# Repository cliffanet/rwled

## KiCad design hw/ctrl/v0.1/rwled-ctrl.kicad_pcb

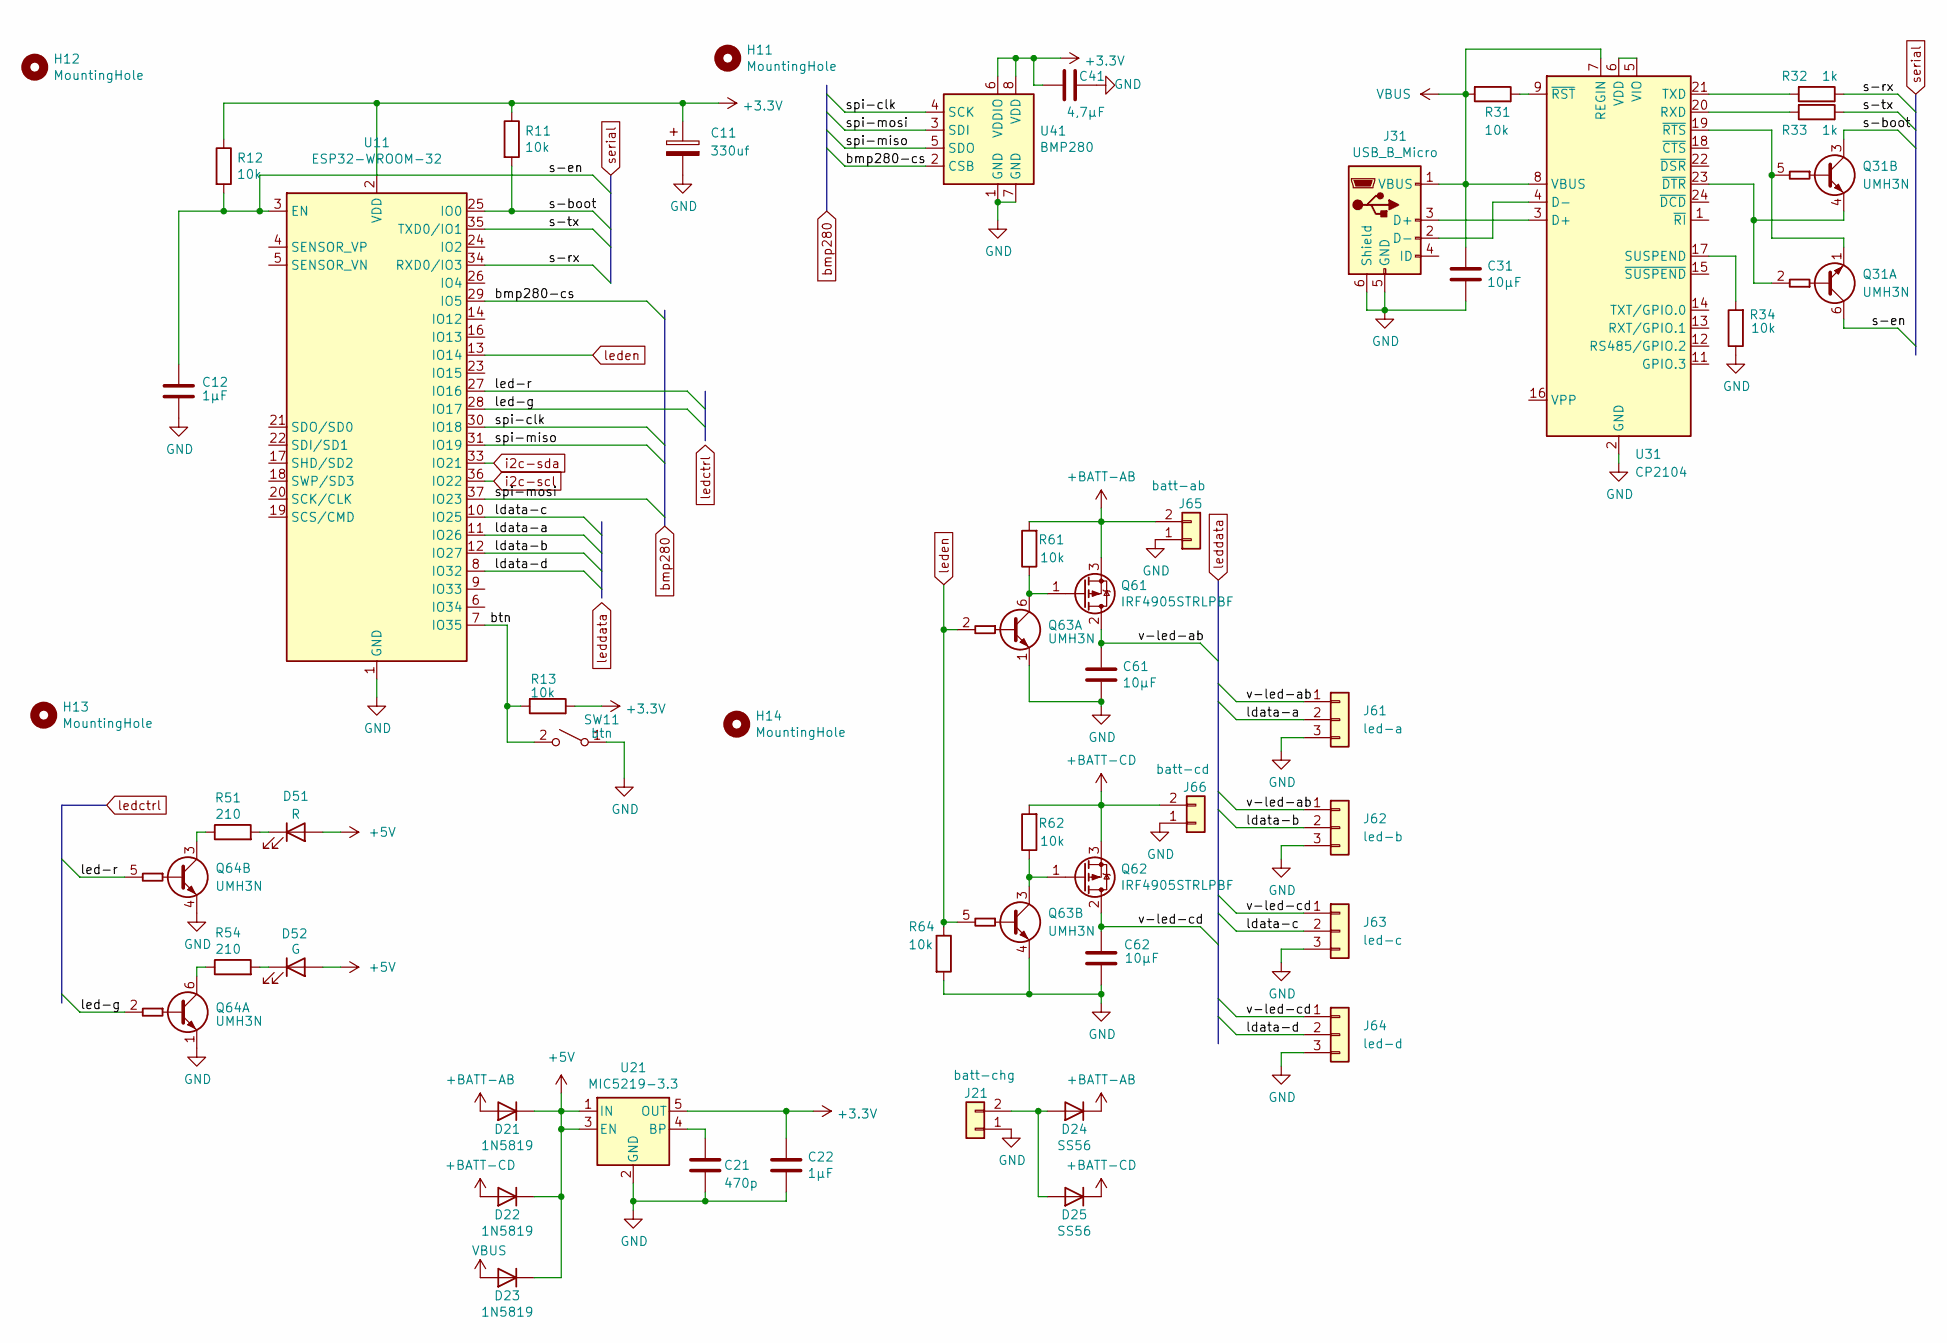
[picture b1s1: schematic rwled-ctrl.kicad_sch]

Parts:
C11: 330uf; CP_EIA-7343-20_Kemet-V
C12, C22: 1μF; C_0805_2012Metric
C21: 470p; C_0805_2012Metric
C31, C61, C62: 10μF; C_0805_2012Metric
C41: 4,7μF; C_0805_2012Metric
D21, D22, D23: 1N5819; D_SOD-323
D24, D25: SS56; D_SMA
D51: R; LED_D3.0mm
D52: G; LED_D3.0mm
H11, H12, H13, H14: MountingHole; MountingHole_3.2mm_M3
J21: batt-chg; AMASS_XT30U-M_1x02_P5.0mm_Vertical
J31: USB_B_Micro; USB_Micro-B_Molex-105017-0001
J61: led-a; JST_XH_S3B-XH-A_1x03_P2.50mm_Horizontal
J62: led-b; JST_XH_S3B-XH-A_1x03_P2.50mm_Horizontal
J63: led-c; JST_XH_S3B-XH-A_1x03_P2.50mm_Horizontal
J64: led-d; JST_XH_S3B-XH-A_1x03_P2.50mm_Horizontal
J65: batt-ab; AMASS_XT30U-F_1x02_P5.0mm_Vertical
J66: batt-cd; AMASS_XT30U-F_1x02_P5.0mm_Vertical
Q31, Q63, Q64: UMH3N; SOT-363_SC-70-6
Q61, Q62: IRF4905STRLPBF; TO-263-2
R11, R12, R13, R31, R34, R61, R62, R64: 10k; R_0805_2012Metric
R32, R33: 1k; R_0805_2012Metric
R51, R54: 210; R_1206_3216Metric
SW11: btn; SW_Push_1P1T_NO_6x6mm_H9.5mm
U11: ESP32-WROOM-32
U21: MIC5219-3.3; SOT-23-5
U31: CP2104; QFN-24-1EP_4x4mm_P0.5mm_EP2.6x2.6mm
U41: BMP280; Bosch_LGA-8_2x2.5mm_P0.65mm_ClockwisePinNumbering

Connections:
+3.3V: C11.1, C22.1, C41.1, R11.1, R12.1, R13.1, U11.2 (VDD), U21.5 (OUT), U41.6 (VDDIO), U41.8 (VDD)
+5V: D21.1 (K), D22.1 (K), D23.1 (K), D51.2 (A), D52.2 (A), U21.1 (IN), U21.3 (EN)
+BATT-AB: D21.2 (A), D24.1 (K), J65.2, Q61.3 (S), R61.2
+BATT-CD: D22.2 (A), D25.1 (K), J66.2, Q62.3 (S), R62.2
/bmp280-cs: U11.29 (IO5), U41.2 (CSB)
/btn: R13.2, SW11.2 (B), U11.7 (IO35)
/ldata-a: J61.2, U11.11 (IO26)
/ldata-b: J62.2, U11.12 (IO27)
/ldata-c: J63.2, U11.10 (IO25)
/ldata-d: J64.2, U11.8 (IO32)
/led-g: Q64.2 (B1), U11.28 (IO17)
/led-r: Q64.5 (B2), U11.27 (IO16)
/s-boot: Q31.3 (C2), R11.2, U11.25 (IO0)
/s-en: C12.1, Q31.6 (C1), R12.2, U11.3 (EN)
/s-rx: R32.1, U11.34 (RXD0/IO3)
/s-tx: R33.1, U11.35 (TXD0/IO1)
/spi-clk: U11.30 (IO18), U41.4 (SCK)
/spi-miso: U11.31 (IO19), U41.5 (SDO)
/spi-mosi: U11.37 (IO23), U41.3 (SDI)
/v-led-ab: C61.1, J61.1, J62.1, Q61.2 (D)
/v-led-cd: C62.2, J63.1, J64.1, Q62.2 (D)
GND: C11.2, C12.2, C21.2, C22.2, C31.2, C41.2, C61.2, C62.1, J21.1, J31.5 (GND), J31.6 (Shield), J61.3, J62.3, J63.3, J64.3, J65.1, J66.1, Q63.1 (E1), Q63.4 (E2), Q64.1 (E1), Q64.4 (E2), R34.1, R64.2, SW11.1 (A), U11.1 (GND), U11.15 (GND), U11.38 (GND), U11.39 (GND), U21.2 (GND), U31.2 (GND), U31.25 (GND), U41.1 (GND), U41.7 (GND)
unnamed: D24.2 (A), D25.2 (A), J21.2
unnamed: D51.1 (K), R51.2
unnamed: D52.1 (K), R54.2
unnamed: J31.3 (D+), U31.3 (D+)
unnamed: J31.2 (D-), U31.4 (D-)
unnamed: Q31.2 (B1), Q31.4 (E2), U31.23 (~DTR)
unnamed: Q31.1 (E1), Q31.5 (B2), U31.19 (~RTS)
unnamed: Q61.1 (G), Q63.6 (C1), R61.1
unnamed: Q62.1 (G), Q63.3 (C2), R62.1
unnamed: Q64.6 (C1), R54.1
unnamed: Q64.3 (C2), R51.1
unnamed: C21.1, U21.4 (BP)
unnamed: R33.2, U31.20 (RXD)
unnamed: R34.2, U31.17 (SUSPEND)
unnamed: R32.2, U31.21 (TXD)
unnamed: U31.5 (VIO), U31.6 (VDD)
unnamed: R31.1, U31.9 (~RST)
VBUS: C31.1, D23.2 (A), J31.1 (VBUS), R31.2, U31.7 (REGIN), U31.8 (VBUS)
i2c-scl: U11.36 (IO22)
i2c-sda: U11.33 (IO21)
leden: Q63.2 (B1), Q63.5 (B2), R64.1, U11.13 (IO14)

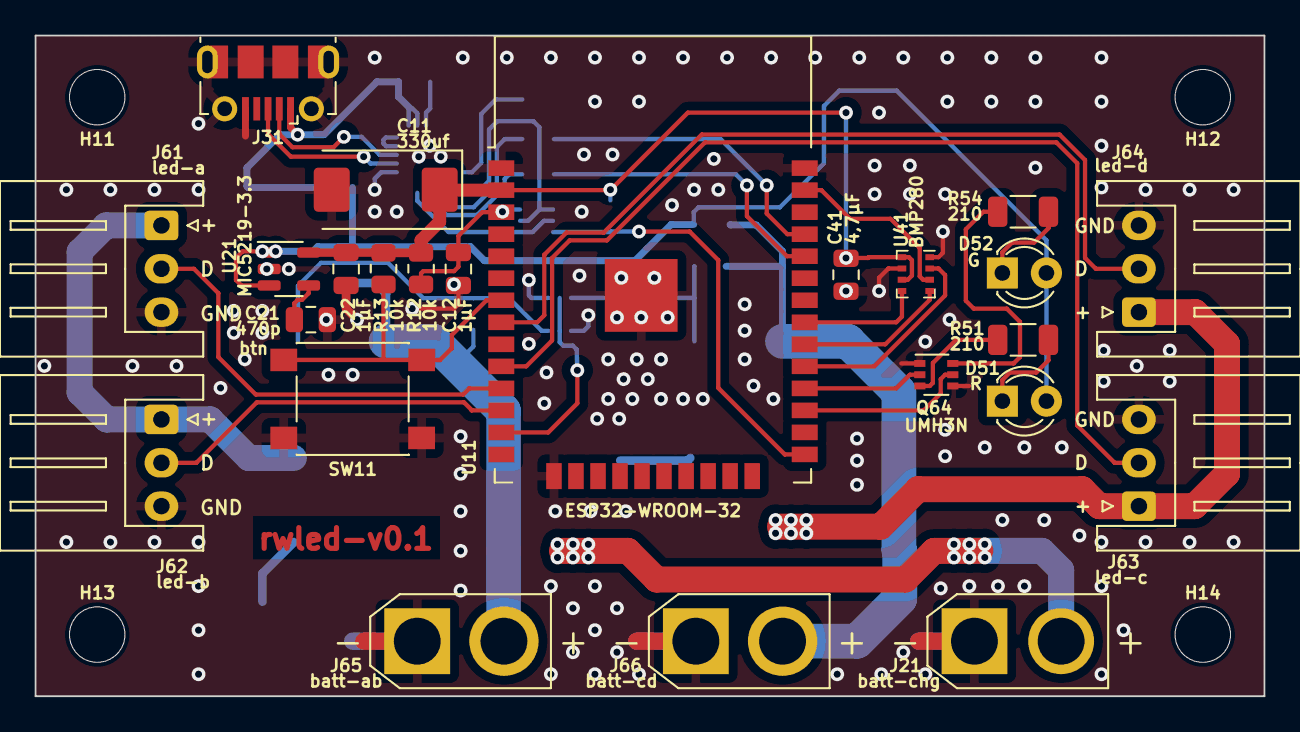
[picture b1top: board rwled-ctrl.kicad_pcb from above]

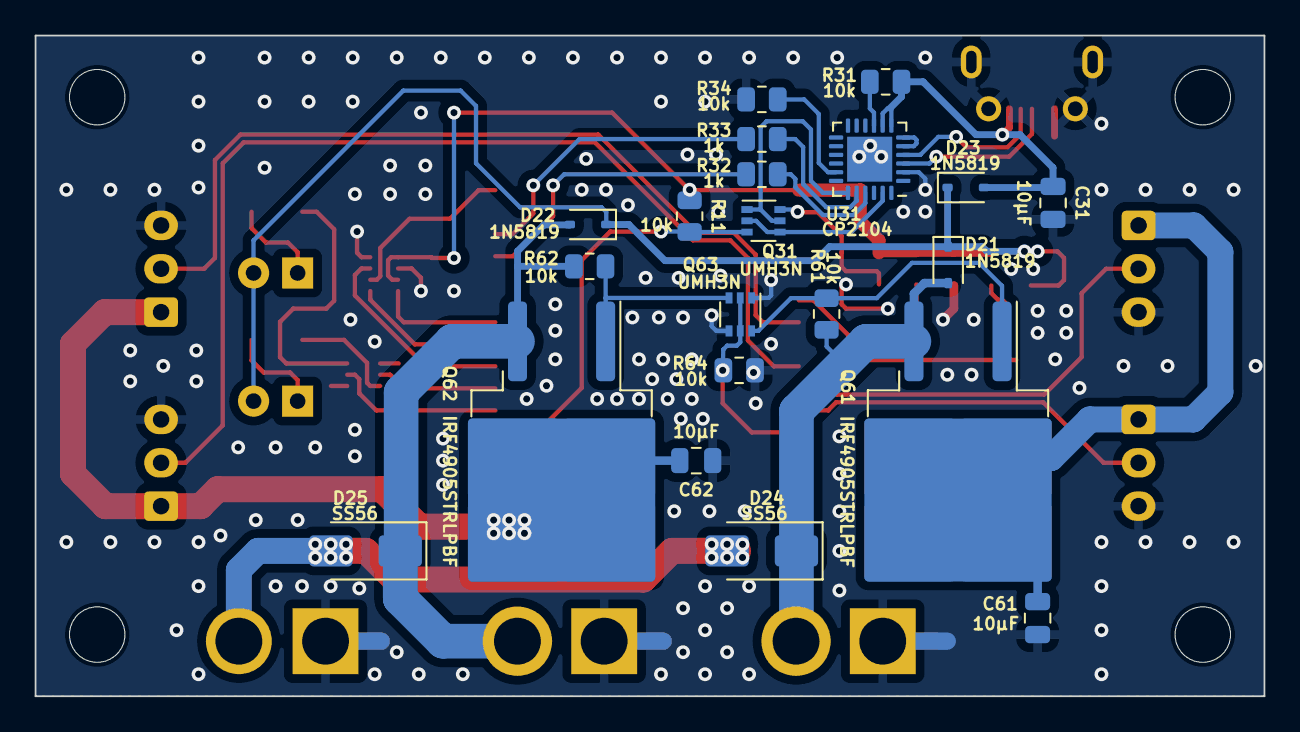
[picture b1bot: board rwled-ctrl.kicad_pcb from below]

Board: 2 copper layers, 70.9 x 38.1 mm, 49 parts (21 on the bottom side), 41 nets.

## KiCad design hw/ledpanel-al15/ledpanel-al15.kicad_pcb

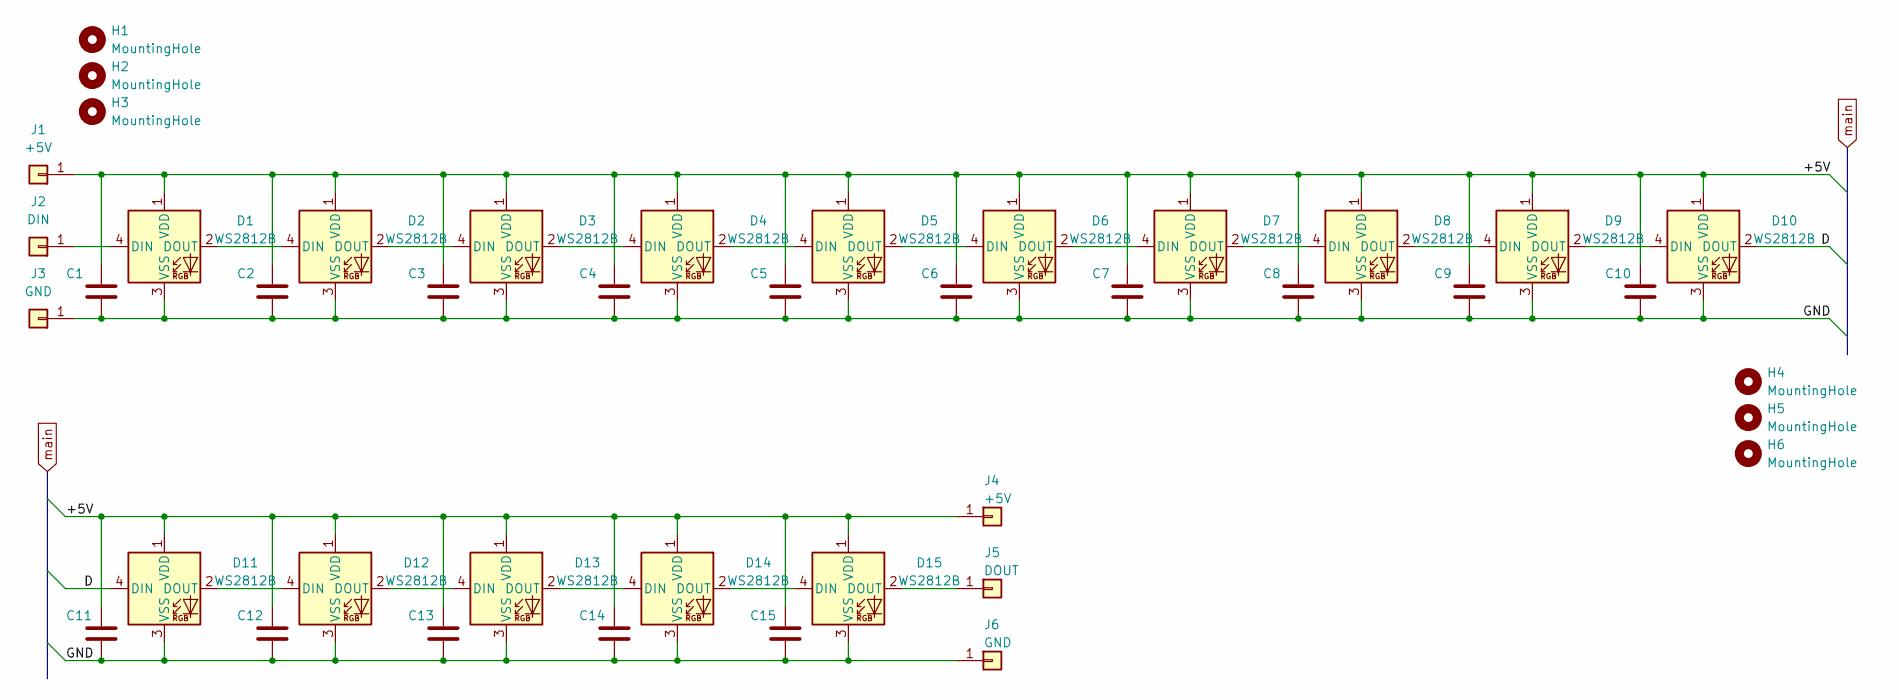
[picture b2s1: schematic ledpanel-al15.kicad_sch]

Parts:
C1, C2, C3, C4, C5, C6, C7, C8, C9, C10, C11, C12, C13, C14, C15: C; C_0805_2012Metric
D1, D2, D3, D4, D5, D6, D7, D8, D9, D10, D11, D12, D13, D14, D15: WS2812B; LED_WS2812B_PLCC4_5.0x5.0mm_P3.2mm
H1, H2, H3, H4, H5, H6: MountingHole; MountingHole_2.1mm
J1, J4: +5V; SolderWirePad_1x01_SMD_1x2mm
J2: DIN; SolderWirePad_1x01_SMD_1x2mm
J3, J6: GND; SolderWirePad_1x01_SMD_1x2mm
J5: DOUT; SolderWirePad_1x01_SMD_1x2mm

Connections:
/+5V: C1.1, C2.1, C3.1, C4.1, C5.1, C6.1, C7.1, C8.1, C9.1, C10.1, C11.1, C12.1, C13.1, C14.1, C15.1, D1.1 (VDD), D2.1 (VDD), D3.1 (VDD), D4.1 (VDD), D5.1 (VDD), D6.1 (VDD), D7.1 (VDD), D8.1 (VDD), D9.1 (VDD), D10.1 (VDD), D11.1 (VDD), D12.1 (VDD), D13.1 (VDD), D14.1 (VDD), D15.1 (VDD), J1.1, J4.1
/D: D10.2 (DOUT), D11.4 (DIN)
/GND: C1.2, C2.2, C3.2, C4.2, C5.2, C6.2, C7.2, C8.2, C9.2, C10.2, C11.2, C12.2, C13.2, C14.2, C15.2, D1.3 (VSS), D2.3 (VSS), D3.3 (VSS), D4.3 (VSS), D5.3 (VSS), D6.3 (VSS), D7.3 (VSS), D8.3 (VSS), D9.3 (VSS), D10.3 (VSS), D11.3 (VSS), D12.3 (VSS), D13.3 (VSS), D14.3 (VSS), D15.3 (VSS), J3.1, J6.1
unnamed: D1.4 (DIN), J2.1
unnamed: D1.2 (DOUT), D2.4 (DIN)
unnamed: D2.2 (DOUT), D3.4 (DIN)
unnamed: D3.2 (DOUT), D4.4 (DIN)
unnamed: D4.2 (DOUT), D5.4 (DIN)
unnamed: D5.2 (DOUT), D6.4 (DIN)
unnamed: D6.2 (DOUT), D7.4 (DIN)
unnamed: D7.2 (DOUT), D8.4 (DIN)
unnamed: D8.2 (DOUT), D9.4 (DIN)
unnamed: D9.2 (DOUT), D10.4 (DIN)
unnamed: D11.2 (DOUT), D12.4 (DIN)
unnamed: D12.2 (DOUT), D13.4 (DIN)
unnamed: D13.2 (DOUT), D14.4 (DIN)
unnamed: D14.2 (DOUT), D15.4 (DIN)
unnamed: D15.2 (DOUT), J5.1

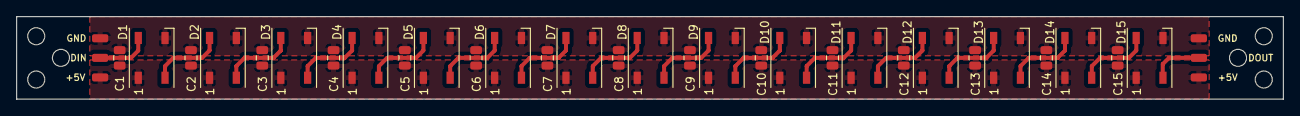
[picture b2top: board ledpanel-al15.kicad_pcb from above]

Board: 2 copper layers, 156.1 x 10.2 mm, 42 parts (0 on the bottom side), 18 nets.

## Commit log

2023-10-21 design - каркас приложения для создания сцен
2023-10-21 design - воспроизведение и список элементов
2023-10-22 design - добавление/удаление элементов сделано через меню
2023-10-22 design - подтверждение удаления элементов
2023-10-23 design - отрисовка участника и перетаскивание
2023-10-23 design - курсор для перетаскивания
2023-10-31 hw led20
2023-10-31 hw led20 - поправлены зоны питания
2023-10-31 hw ctrl - схема (не проверена)
2023-11-04 hw ctrl - плата - расставлены элементы
2023-11-04 hw ctrl - плата доразведена
2023-11-05 hw led20 - перечерчен гербер
2023-11-05 hw - сделаны led15 и led10
2023-11-25 hw - v0.1-archive
2023-11-25 rwdesign - загрузка json - объекты
2023-11-26 rwdesign - загрузка json - движение
2023-11-27 rwdesign - доработки движения
2023-11-27 rwdesign - вращение
2023-12-02 rwdesign - инклюд из другого файла и отрисовка номера
2023-12-02 rwdesign - отрисовка расположения светодиодов
2023-12-02 rwdesign - свет - базовая отрисовка
2023-12-03 rwdesign - свет - sector
2023-12-03 rwdesign - при загрузке нового файла - выставлять ему tm
2023-12-03 rwdesign - свет - параметр ожидания после завершения анимации
2023-12-03 rwdesign - примеры
2023-12-03 rwdesign - получение нужного цвета для светодиодов
2023-12-05 rwdesign - точечное рисование света на основе получения цвета в каждой точке
2023-12-10 rwdesign - зацикливание
2023-12-10 rwdesign - сохранение персональных led-файлов
2023-12-16 rwdesign - led-файлы - изменён формат, теперь каждый диод построчно
2023-12-16 fw - общий каркас и парсер из консоли (теряет буфер, нужен другой канал)
2023-12-16 wifi + парсер через веб-аплоад
2023-12-17 доработки парсинга
2023-12-17 сохранение потока во временный файл и завершение wifi-upload-сессии
2023-12-17 проигрывание сценария на светодиодах, пока без зацикливания
2023-12-23 зацикливание воспроизведения
2023-12-23 опциональное форматирование при аплоаде
2023-12-23 обработчик кнопки
2023-12-23 индикация светодиодами
2023-12-26 корпус
2023-12-26 работа с файлами - напрямую в esp-idf
2023-12-28 переделано управление кнопкой и индикацией + имя wifi содержит my-num
2023-12-29 включение/выключение
2023-12-30 корпус - доработки
2024-01-01 плата - добавлен "*" для bmp280
2024-01-02 подключён высотомер
2024-01-03 реструктуризация модулей
2024-01-03 каркас wifidirect - прямого общения по wifi
2024-01-04 бинарная упаковка данных в пакеты
2024-01-04 синхронизация на тестовых светодиодах для отладки
2024-01-13 корпус - правка диаметра отверстий верхней части
2024-01-13 обновлённая версия altcalc
2024-01-13 переработан алгоритм синхронизации и старта сценария
2024-01-14 режим таймера - так же синхронизировать
2024-01-14 доработки режима canopy
2024-01-14 доработка индикации вкл/выкл питания
2024-01-15 рефакторинг ledstream - вынесены: инициализация файловой системы, парсер/сохранятор из текстового потока во временный файл
2024-01-16 рефакторинг ledstream - вынесены: управление светодиодными лентами (вкл всей ленты в определённый цвет) и заготовка под чтение сценария
2024-01-17 рефакторинг ledstream - вынесен сценарий
2024-01-18 доработки по режимам подсветки лент
2024-01-28 баги по воспроизведению сценария
2024-01-29 example - test
2024-02-04 example - starwars
2024-02-04 мьютексы - попытка решить случайные зависания при остановке сценария
2024-02-06 поправлены световые режимы
2024-02-06 тест
2024-02-11 example - 2way / 4way
2024-02-18 hw - доработки платы под oled-дисплей
2024-02-18 hw - подвинуты отверстия din/dout на светодиодных лентах
2024-02-18 Рассчёт сегментов светодиодных лент
2024-02-19 hw - архив доработанных и отправленных в заказ плат
2024-02-26 box - архив v0.1
2024-03-09 rwdesign - доработки по загрузке файлов
2024-03-09 переименование файлов в примерах
2024-03-11 буфер чтения сценария переделан под догрузку отдельным потоком. Осталось делать seek
2024-03-12 буфер чтения сценария - доработан loop/seek
2024-03-13 блок заполнения данных о цветах светодиодов в массивах (подготовка к своему управлению светодиодами)
2024-03-14 своя отправка команд на светодиоды, но нужно ещё отладить зависания show-потока.
2024-03-15 ledlight - воркер формирования массивов цветов светодиодов (будем сюда так же выносить всю работу с самими лентами)
2024-03-16 допереработан блок отображения сценария - перевели всё на воркеры, а чтение из файла в буфер осталось отдельным потоком
2024-03-16 доработки по синхронизации (нужно отлаживать)
2024-03-16 display - высотомер и mynum
2024-03-17 display - режим светодиодного сценария, вкл/выкл питания
2024-03-17 display - состояние wifiserver
2024-03-17 worker interval = 100ms
2024-03-17 worker interval = 30ms - вернули обратно с небольшими доработками (пропуски перерисовки дисплея и более медленная отправка сигналов на светодиодные ленты)
2024-03-18 поправлены баги altcalc / ringsimple
2024-03-18 altcalc - обновление
2024-04-01 hwver (есть пересечения пинов в разных версиях)
2024-04-06 индикатор заряда батарей + баг перезагрузки при отсутствии сценария
2024-04-20 доработки altcalc
2024-06-04 доработки инициализации дисплея
2024-06-04 корпус под дисплей
2024-06-04 корпус зарядника
2024-09-29 тестирование светодиодов при включении
2024-10-18 описание параметров лент
2024-11-12 данные по креплению приборов
